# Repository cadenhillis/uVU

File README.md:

# uVU
A tiny analog VU meter

Uses the LM3915 to do a fun little VU display on an LED bargraph.

The pcb is a little hard to assemble, but bending the bargraph's pins out before soldering everything helps.

I didn't get great results with the two tuning pots -- they seemed to almost fight eachother.
Maybe adding some smoothing to make the sound wave more DC-like or only having 1 pot in the future will help things.

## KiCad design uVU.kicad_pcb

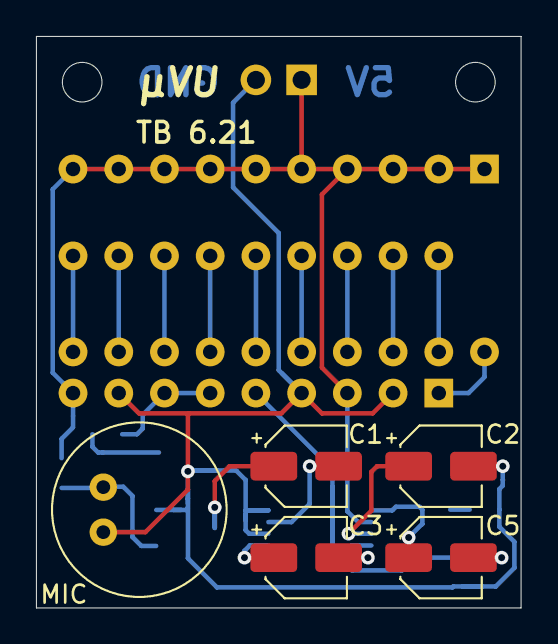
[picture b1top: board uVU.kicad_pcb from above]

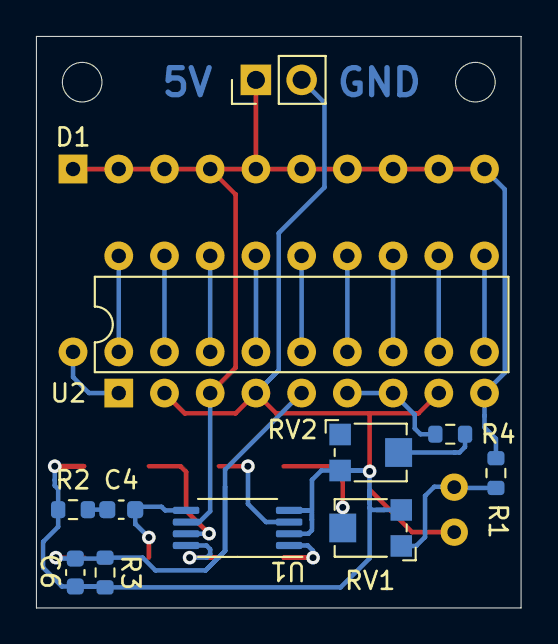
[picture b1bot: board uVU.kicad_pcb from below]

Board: 2 copper layers, 26.9 x 31.8 mm, 19 parts (11 on the bottom side), 23 nets.

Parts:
C1, C2, C3, C5: 10uF; CP_Elec_4x3
C4: 47nF; C_0603_1608Metric
C6: 0.1uF; C_0603_1608Metric
D1: DC10; DIP-16_W10.16mm
H1: M2.2; MountingHole_2.2mm_M2
H2: M2.5; MountingHole_2.2mm_M2
J1: SSW-102-01-T-S; PinHeader_1x02_P2.54mm_Vertical
MIC: CMA-6542PF
R1: 2.2k; R_0603_1608Metric
R2: 10R; R_0603_1608Metric
R3: 10k; R_0603_1608Metric
R4: 1k; R_0603_1608Metric
RV1, RV2: 10k; Potentiometer_Bourns_TC33X_Vertical
U1: LM386MMX-1/NOPB; TSSOP-8_4.4x3mm_P0.65mm
U2: LM3915; DIP-18_W7.62mm

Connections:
+5V: D1.1, D1.2, D1.3, D1.4, D1.5, D1.6, D1.7, D1.8, D1.9, D1.10, J1.1, R1.1, U1.6, U2.3, U2.9
/Vsig: C5.2, C6.1, R3.1, U2.5
GND: C2.2, C6.2, J1.2, MIC.1, R2.2, R3.2, RV1.3, RV2.3, U1.2, U1.4, U2.2, U2.4, U2.8
unnamed: C1.1, RV1.2
unnamed: C1.2, U1.3
unnamed: C2.1, U1.7
unnamed: C3.1, U1.1
unnamed: C3.2, U1.8
unnamed: C4.1, C5.1, U1.5
unnamed: C4.2, R2.1
unnamed: D1.11, U2.10
unnamed: D1.12, U2.11
unnamed: D1.13, U2.12
unnamed: D1.14, U2.13
unnamed: D1.15, U2.14
unnamed: D1.16, U2.15
unnamed: D1.17, U2.16
unnamed: D1.18, U2.17
unnamed: D1.19, U2.18
unnamed: D1.20, U2.1
unnamed: MIC.2, R1.2, RV1.1
unnamed: R4.1, U2.6, U2.7
unnamed: R4.2, RV2.2
